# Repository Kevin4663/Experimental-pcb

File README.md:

# Experimental-pcb
 kevins new pcb

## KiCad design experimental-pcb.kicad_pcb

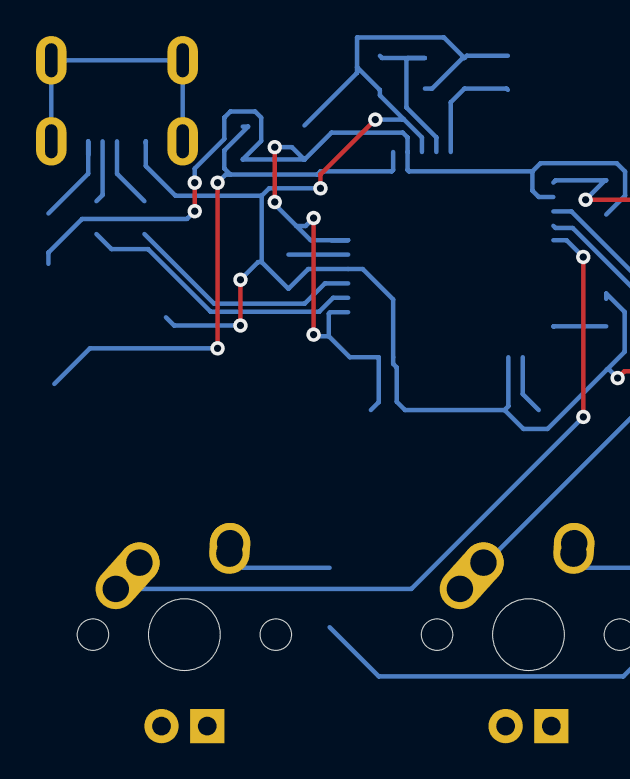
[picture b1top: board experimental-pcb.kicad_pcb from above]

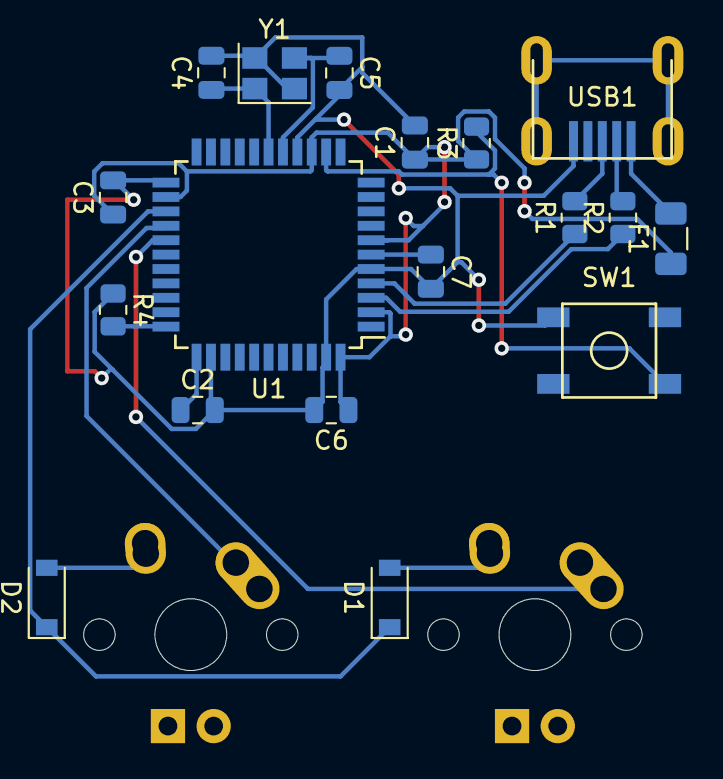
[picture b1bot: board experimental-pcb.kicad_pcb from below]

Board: 2 copper layers, 20 parts (18 on the bottom side), 17 nets.

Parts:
C1, C2, C3: 0.1uF; C_0805_2012Metric
C4, C5: 22pF; C_0805_2012Metric
C6: 10uF; C_0805_2012Metric
C7: 1uF; C_0805_2012Metric
D1, D2: SOD_123; D_SOD-123
F1: Polyfuse_Small; Fuse_1206_3216Metric
MX1, MX2: MX-NoLED; MX-1U
R1, R2: 22; R_0805_2012Metric
R3, R4: 10k; R_0805_2012Metric
SW1: SW_Push; SKQG-1155865
U1: ATmega32U4-AU; TQFP-44_10x10mm_P0.8mm
USB1: Molex-0548190589
Y1: 16MHz; Crystal_SMD_3225-4Pin_3.2x2.5mm

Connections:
+5V: C1.1, C2.1, C3.1, C6.1, F1.1, R3.1, U1.2, U1.7, U1.14, U1.24, U1.34, U1.44
COL0: MX1.1, U1.27
COL1: MX2.1, U1.26
D+: R1.2, USB1.3
D-: R2.2, USB1.4
GND: C1.2, C2.2, C3.2, C4.2, C5.2, C6.2, C7.2, R4.1, SW1.1, U1.5, U1.15, U1.23, U1.35, U1.43, USB1.1, Y1.2, Y1.4
unnamed: C4.1, U1.17, Y1.1
unnamed: C5.1, U1.16, Y1.3
unnamed: C7.1, U1.6
unnamed: D1.2, MX1.2
unnamed: D2.2, MX2.2
unnamed: R1.1, U1.4
unnamed: R2.1, U1.3
unnamed: R3.2, SW1.2, U1.13
unnamed: R4.2, U1.33
ROW0: D1.1, D2.1, U1.25
VCC: F1.2, USB1.5

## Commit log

2020-12-12 Add submodule
2020-12-12 Add Submodules
2020-12-12 final
